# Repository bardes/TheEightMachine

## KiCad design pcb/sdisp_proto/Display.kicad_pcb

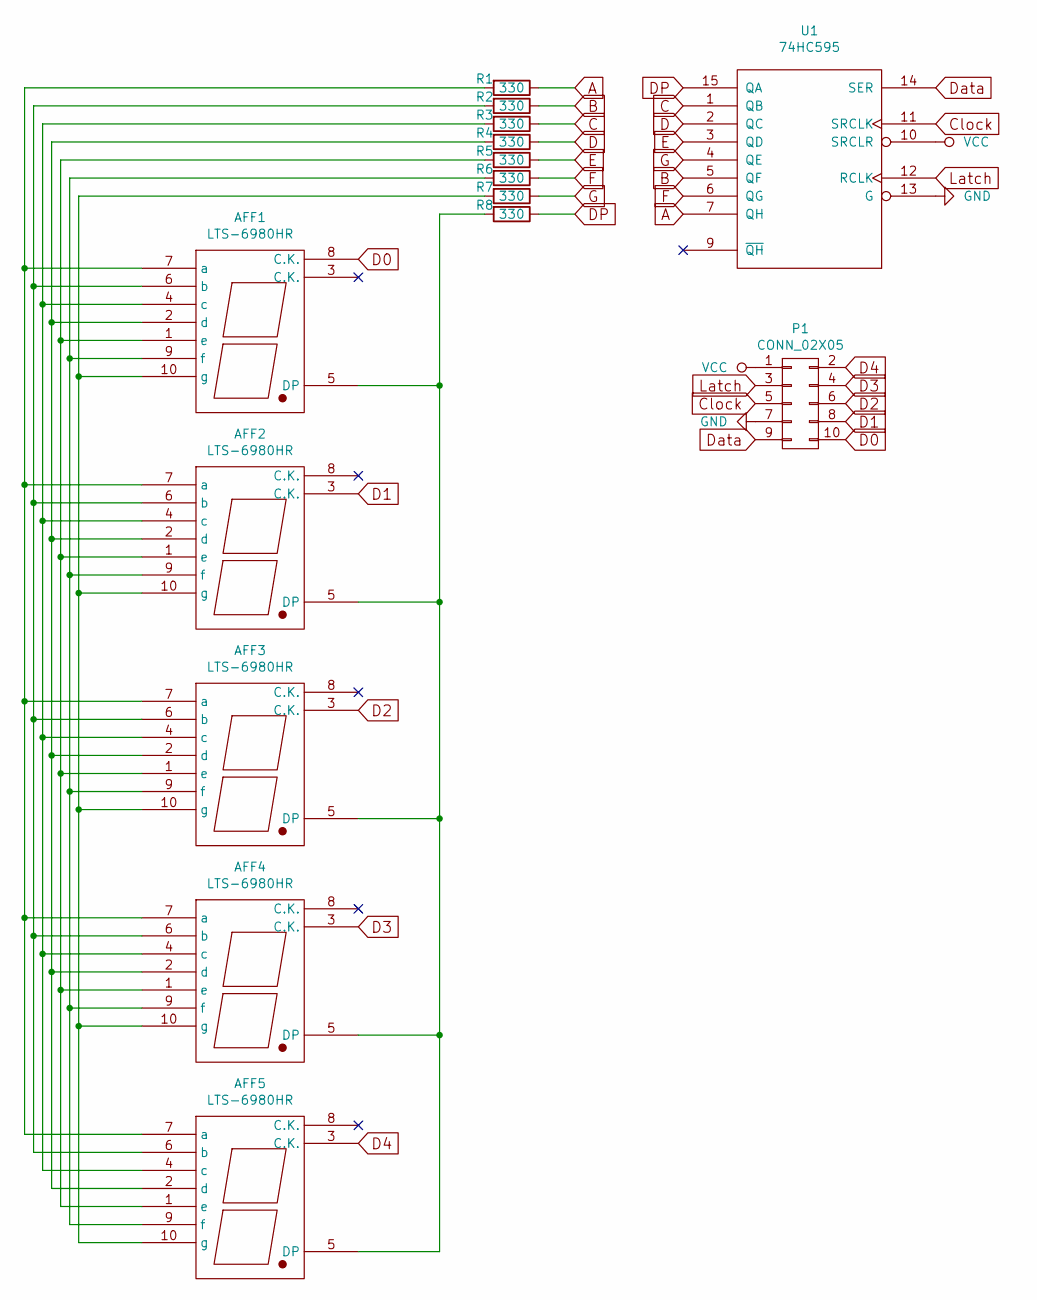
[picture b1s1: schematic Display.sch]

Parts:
AFF1, AFF2, AFF3, AFF4, AFF5: LTS-6980HR; 7SegmentLED_LTS6760_LTS6780
P1: CONN_02X05; Pin_Header_Straight_2x05
R1, R2, R3, R4, R5, R6, R7, R8: 330; R_0805_HandSoldering
U1: 74HC595; SOIC-16_3.9x9.9mm_Pitch1.27mm

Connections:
A: R1.1, U1.7 (QH)
B: R2.1, U1.5 (QF)
C: R3.1, U1.1 (QB)
Clock: P1.5, U1.11 (SRCLK)
D: R4.1, U1.2 (QC)
D0: AFF1.8 (C.K.), P1.10
D1: AFF2.3 (C.K.), P1.8
D2: AFF3.3 (C.K.), P1.6
D3: AFF4.3 (C.K.), P1.4
D4: AFF5.3 (C.K.), P1.2
DP: R8.1, U1.15 (QA)
Data: P1.9, U1.14 (SER)
E: R5.1, U1.3 (QD)
F: R6.1, U1.6 (QG)
G: R7.1, U1.4 (QE)
GND: P1.7, U1.8 (GND), U1.13 (G)
Latch: P1.3, U1.12 (RCLK)
unnamed: AFF1.1 (e), AFF2.1 (e), AFF3.1 (e), AFF4.1 (e), AFF5.1 (e), R5.2
unnamed: AFF1.2 (d), AFF2.2 (d), AFF3.2 (d), AFF4.2 (d), AFF5.2 (d), R4.2
unnamed: AFF1.4 (c), AFF2.4 (c), AFF3.4 (c), AFF4.4 (c), AFF5.4 (c), R3.2
unnamed: AFF1.5 (DP), AFF2.5 (DP), AFF3.5 (DP), AFF4.5 (DP), AFF5.5 (DP), R8.2
unnamed: AFF1.6 (b), AFF2.6 (b), AFF3.6 (b), AFF4.6 (b), AFF5.6 (b), R2.2
unnamed: AFF1.7 (a), AFF2.7 (a), AFF3.7 (a), AFF4.7 (a), AFF5.7 (a), R1.2
unnamed: AFF1.9 (f), AFF2.9 (f), AFF3.9 (f), AFF4.9 (f), AFF5.9 (f), R6.2
unnamed: AFF1.10 (g), AFF2.10 (g), AFF3.10 (g), AFF4.10 (g), AFF5.10 (g), R7.2
VCC: P1.1, U1.10 (SRCLR), U1.16 (VCC)

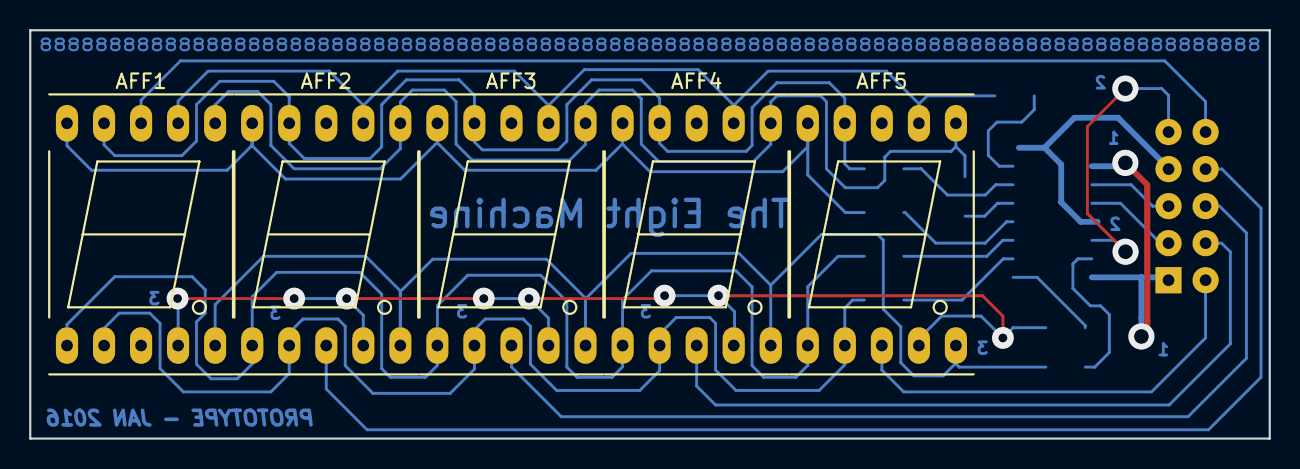
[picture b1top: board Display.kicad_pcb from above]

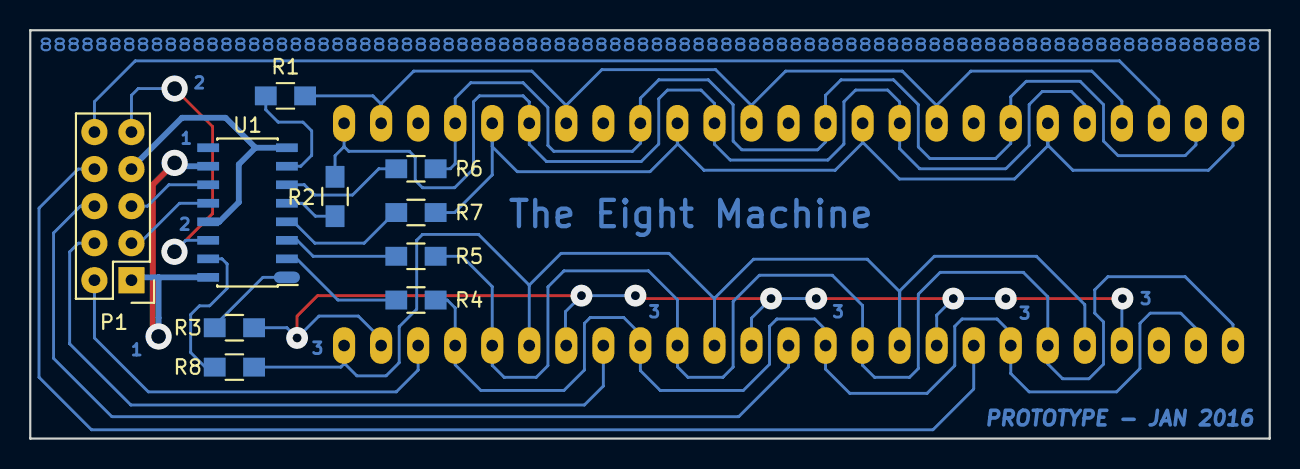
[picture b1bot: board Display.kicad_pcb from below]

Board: 2 copper layers, 85.0 x 28.0 mm, 15 parts (10 on the bottom side), 26 nets.

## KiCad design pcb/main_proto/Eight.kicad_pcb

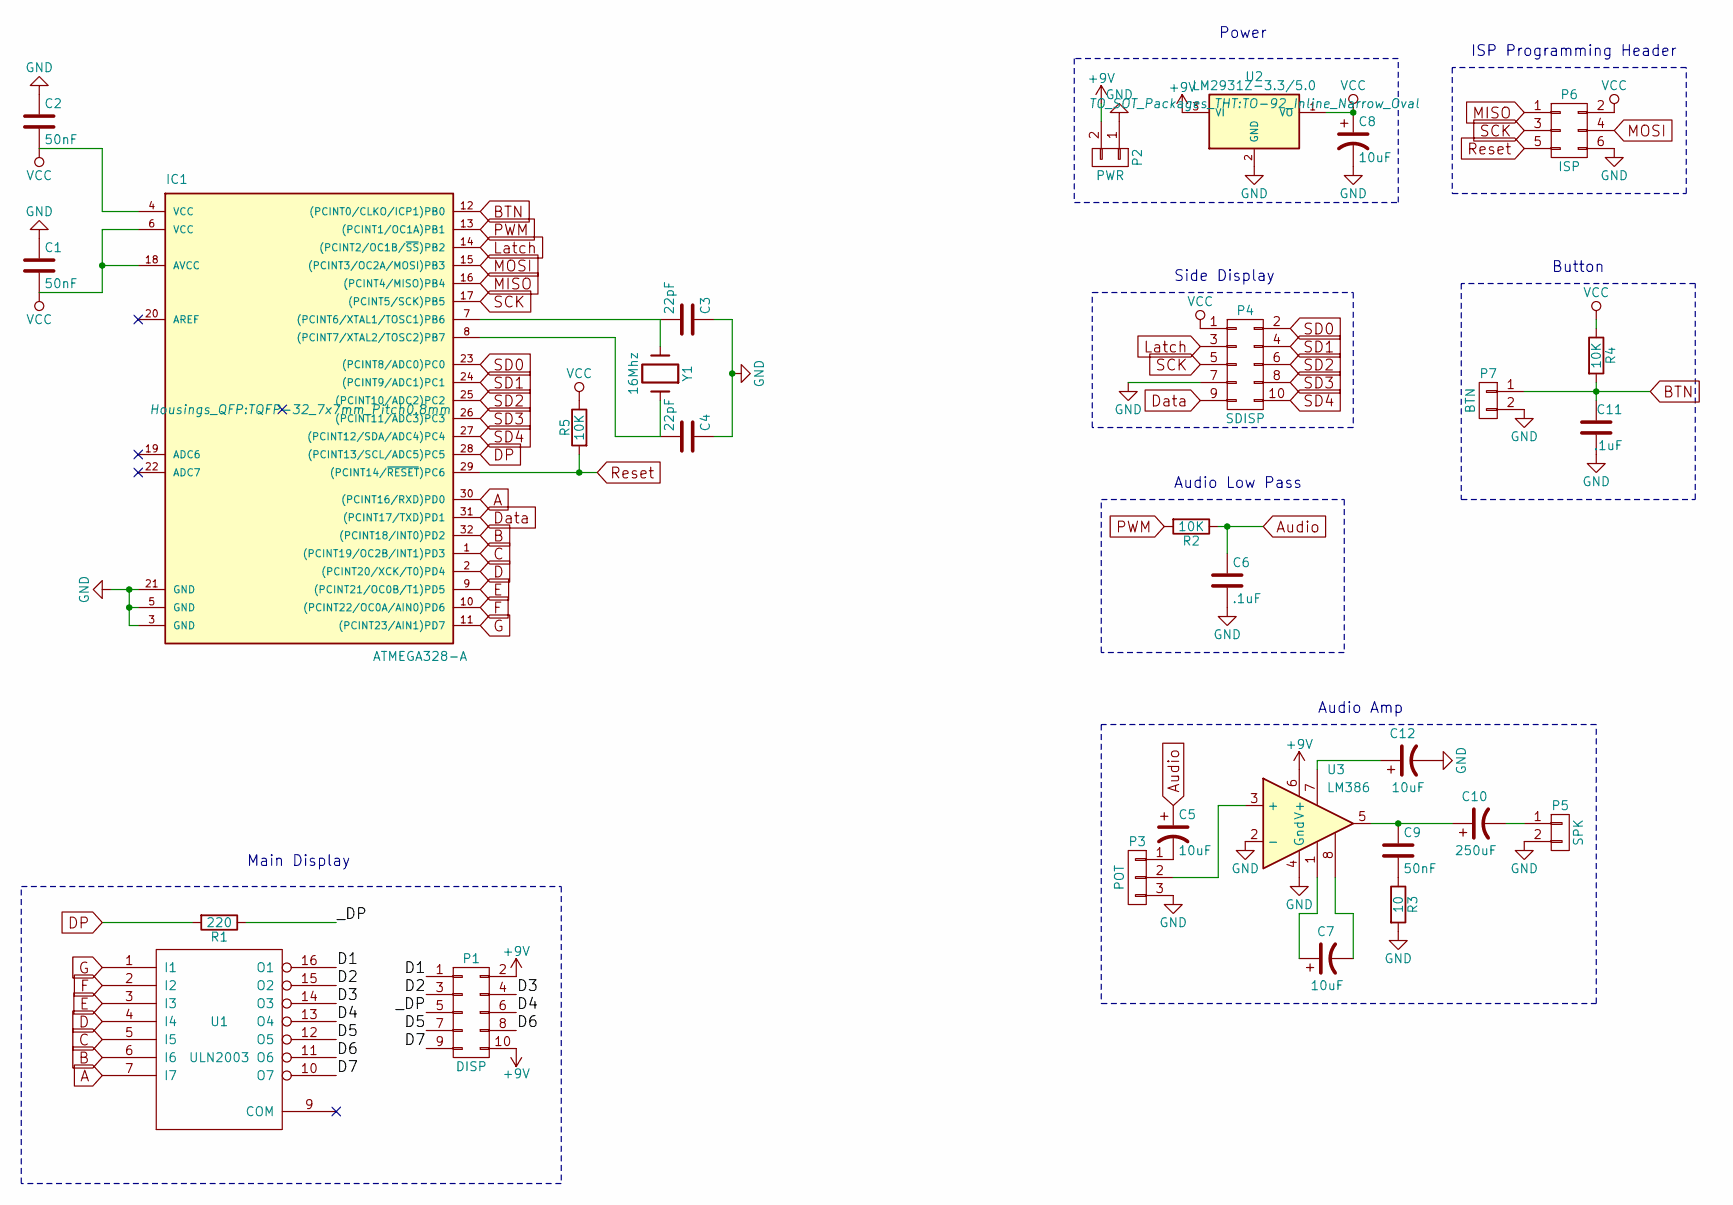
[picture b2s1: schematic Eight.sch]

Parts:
C1, C2, C9: 50nF; C_Rect_L7_W2.5_P5
C3, C4: 22pF; C_Rect_L7_W2.5_P5
C5, C7, C8, C12: 10uF; C_Radial_D10_L16_P5
C6, C11: .1uF; C_Rect_L7_W2.5_P5
C10: 250uF; C_Radial_D10_L16_P5
IC1: ATMEGA328-A; TQFP-32_7x7mm_Pitch0.8mm
P1: DISP; Pin_Header_Straight_2x05
P2: PWR; Pin_Header_Straight_1x02
P3: POT; Pin_Header_Straight_1x03
P4: SDISP; Pin_Header_Straight_2x05
P5: SPK; Pin_Header_Straight_1x02
P6: ISP; Pin_Header_Straight_2x03
P7: BTN; Pin_Header_Straight_1x02
R1: 220; Resistor_Horizontal_RM10mm
R2, R4, R5: 10K; Resistor_Horizontal_RM10mm
R3: 10; Resistor_Horizontal_RM10mm
U1: ULN2003; SOIC-16_3.9x9.9mm_Pitch1.27mm
U2: LM2931Z-3.3/5.0; TO-92_Inline_Narrow_Oval
U3: LM386; SOIC-8_3.9x4.9mm_Pitch1.27mm
Y1: 16Mhz; Crystal_HC49-U_Vertical

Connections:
+9V: P1.2, P1.10, P2.2, U2.3 (VI), U3.6 (V+)
/D1: P1.1, U1.16 (O1)
/D2: P1.3, U1.15 (O2)
/D3: P1.4, U1.14 (O3)
/D4: P1.6, U1.13 (O4)
/D5: P1.7, U1.12 (O5)
/D6: P1.8, U1.11 (O6)
/D7: P1.9, U1.10 (O7)
/_DP: P1.5, R1.1
A: IC1.30 ((PCINT16/RXD)PD0), U1.7 (I7)
Audio: C5.1, C6.1, R2.1
B: IC1.32 ((PCINT18/INT0)PD2), U1.6 (I6)
BTN: C11.1, IC1.12 ((PCINT0/CLKO/ICP1)PB0), P7.1, R4.2
C: IC1.1 ((PCINT19/OC2B/INT1)PD3), U1.5 (I5)
D: IC1.2 ((PCINT20/XCK/T0)PD4), U1.4 (I4)
DP: IC1.28 ((PCINT13/SCL/ADC5)PC5), R1.2
Data: IC1.31 ((PCINT17/TXD)PD1), P4.9
E: IC1.9 ((PCINT21/OC0B/T1)PD5), U1.3 (I3)
F: IC1.10 ((PCINT22/OC0A/AIN0)PD6), U1.2 (I2)
G: IC1.11 ((PCINT23/AIN1)PD7), U1.1 (I1)
GND: C1.1, C2.1, C3.1, C4.1, C6.2, C8.2, C11.2, C12.2, IC1.3 (GND), IC1.5 (GND), IC1.21 (GND), P2.1, P3.3, P4.7, P5.2, P6.6, P7.2, R3.2, U1.8 (GND), U2.2 (GND), U3.2 (-), U3.4 (Gnd)
Latch: IC1.14 ((PCINT2/OC1B/~SS~)PB2), P4.3
MISO: IC1.16 ((PCINT4/MISO)PB4), P6.1
MOSI: IC1.15 ((PCINT3/OC2A/MOSI)PB3), P6.4
unnamed: C3.2, IC1.7 ((PCINT6/XTAL1/TOSC1)PB6), Y1.2
unnamed: C4.2, IC1.8 ((PCINT7/XTAL2/TOSC2)PB7), Y1.1
unnamed: C5.2, P3.1
unnamed: C7.1, U3.1
unnamed: C7.2, U3.8
unnamed: C9.2, R3.1
unnamed: C9.1, C10.1, U3.5
unnamed: C10.2, P5.1
unnamed: C12.1, U3.7
unnamed: P3.2, U3.3 (+)
PWM: IC1.13 ((PCINT1/OC1A)PB1), R2.2
Reset: IC1.29 ((PCINT14/~RESET~)PC6), P6.5, R5.2
SCK: IC1.17 ((PCINT5/SCK)PB5), P4.5, P6.3
SD0: IC1.23 ((PCINT8/ADC0)PC0), P4.2
SD1: IC1.24 ((PCINT9/ADC1)PC1), P4.4
SD2: IC1.25 ((PCINT10/ADC2)PC2), P4.6
SD3: IC1.26 ((PCINT11/ADC3)PC3), P4.8
SD4: IC1.27 ((PCINT12/SDA/ADC4)PC4), P4.10
VCC: C1.2, C2.2, C8.1, IC1.4 (VCC), IC1.6 (VCC), IC1.18 (AVCC), P4.1, P6.2, R4.1, R5.1, U2.1 (VO)

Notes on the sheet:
ISP Programming Header
Main Display
Audio Low Pass
Side Display
Button
Audio Amp
Power

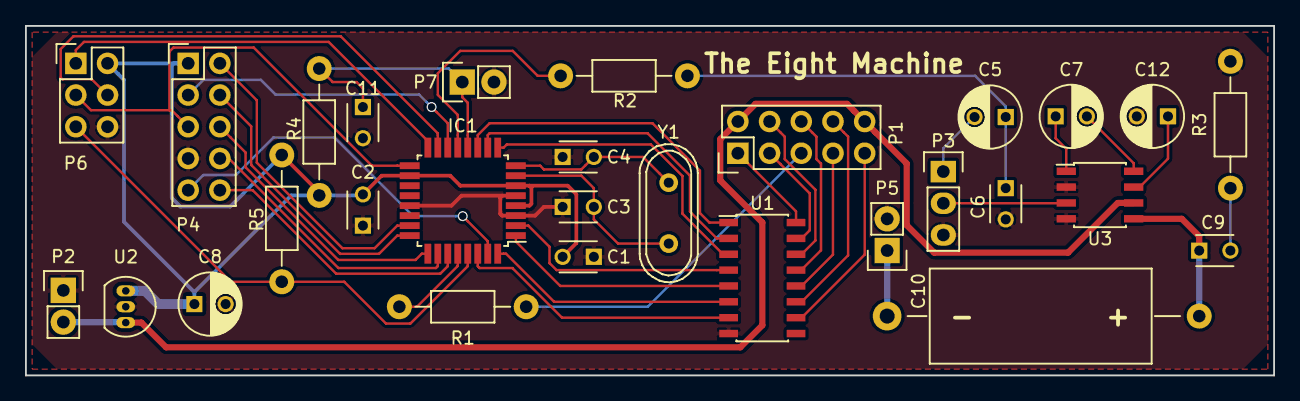
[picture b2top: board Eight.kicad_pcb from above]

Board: 2 copper layers, 100.0 x 28.0 mm, 29 parts (0 on the bottom side), 43 nets.

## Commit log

2016-01-14 Initial commit.
2016-01-14 Added side display
2016-01-14 Fix: Lyout of power section on the schematics.
2016-01-14 Finished side display prototype.
2016-01-22 Bitbang shiftout implementation
2016-01-22 Fix: format and miss by one on shiftout test
2016-01-22 Add: custom clang-format style file
2016-01-22 Fix: Latch is now defined on ports.h
2016-01-22 Mtnc: multdigit.c not needed anymore
    -Updated .gitignore and .clang-format
2016-01-23 Fix: Layout of the pin header on the prototype
